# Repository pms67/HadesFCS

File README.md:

# HADES Flight Control System
**Complete flight control system designed from scratch.** The flight control system is primarily designed for fixed-wing, autonomous drones to enable them to perform tasks autonomously, such as take-off, landing, waypoint navigation, payload delivery, etc.

Every part of this system is designed from first principles! This includes the hardware, firmware (using FreeRTOS), Kalman filtering for state estimation, control algorithms, base station, communication protocol, flight simulator, signal processing, and much, much more.

*Feel free to send me constructive criticism or things you would like me to implement, or even if you would like to help me develop this system!*

Intro video: https://www.youtube.com/watch?v=rLDqQ2L_mUQ
       
---

**Broadly, this repository consists of:**
* Hardware designs (developed using KiCAD).
* Low-level drivers and firmware (FreeRTOS, for the STM32 platform of microcontrollers).
* Higher-level firmware such as communication protocols, control and navigation algorithms, etc.
* Kalman filter designs for state estimation.
* Debugging tools.
* Flight simulator (both 6-DOF and 3-DOF) to test algorithms.

---

**Current repository folder structure:**
* *Calibration:* Raw sensor data useful for checking calibration algorithms (e.g. accelerometer bias, scale factor, etc.).
* *Communication:* UAVLink data protocol for reliably packing and transferring data and commands between the aircraft and a further device (e.g. base station). This could be via telemetry or direct serial links.
* *Control:* Algorithms for dynamic control of the aircraft (e.g. PI, state feedback, etc.).
* *Data:* Collection of various datasets that may be useful for offline testing (e.g. raw IMU data).
* *Debug Software:* Tools for interfacing with the hardware (e.g. to read navigation data).
* *Documentation:* Preliminary documents to detail aspects of the flight  control system.
* *Filtering:* FIR and IIR filter implementations, as well as FIR filter design tool.
* *Firmware:* The core flight control firmware running on the STM32 microcontrollers.
* *Flight Simulator:* 6-DOF and 3-DOF fixed-wing flight simulators developed in Unity. Very useful for testing control logic and algorithms. Requires dynamic model of aircraft.
* *GPS:* NMEA sentence parser, as well as raw GPS data for testing.
* *Ground Control:* Basestations written in C# to send commands to aircraft and receive data via telemetry. Includes moving map, live plots, etc.
* *Hardware:* HADES flight control board design files (schematic, layout, assembly). Hardware consists of sensors, microcontrollers, power electronics, etc. This custom hardware is where the firmware runs on.
* *State Estimation*: Kalman filters (various types: quaternion, Euler, different states estimated) designed in Matlab and exported to C for estimation of states required for feedback control (e.g. attitude, position, etc.).
* *Tests:* Miscallaneous tests go here. For instance, device driver testing, communication protocol tests, etc.

**Note:** Most subfolders include an additional README that further describes its contents.

---

**Disclaimer:** This flight control system is work in progress. Use the files, hardware, and software given in this repository **at your own risk** - especially when conducting live flight tests.

BSD 3-Clause License - Copyright (c) 2019, Philip Salmony - All rights reserved.

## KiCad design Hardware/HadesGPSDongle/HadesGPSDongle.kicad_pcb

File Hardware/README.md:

# HADES Hardware

This folder contains all hardware design files for the HADES flight control system.

Currently, there are three designs:

* *Hades:* Dual STM32-based board containing microcontrollers (F4 and H7), inertial sensors, GPS receiver, power distribution system for servos (up to 9A at 5V). This is the main platform for testing.
* *Hades Micro:* 5cmx5cm flight control board with a single STM32F4. No GPS receiver and limited power distribution.
* *Hades Micro (JLCPCB):* Nearly identical to Hades Micro, however uses SPI instead of I2C for sensor communication. Additionally, nearly all parts are available through LCSC/JLCPCB for assembly.

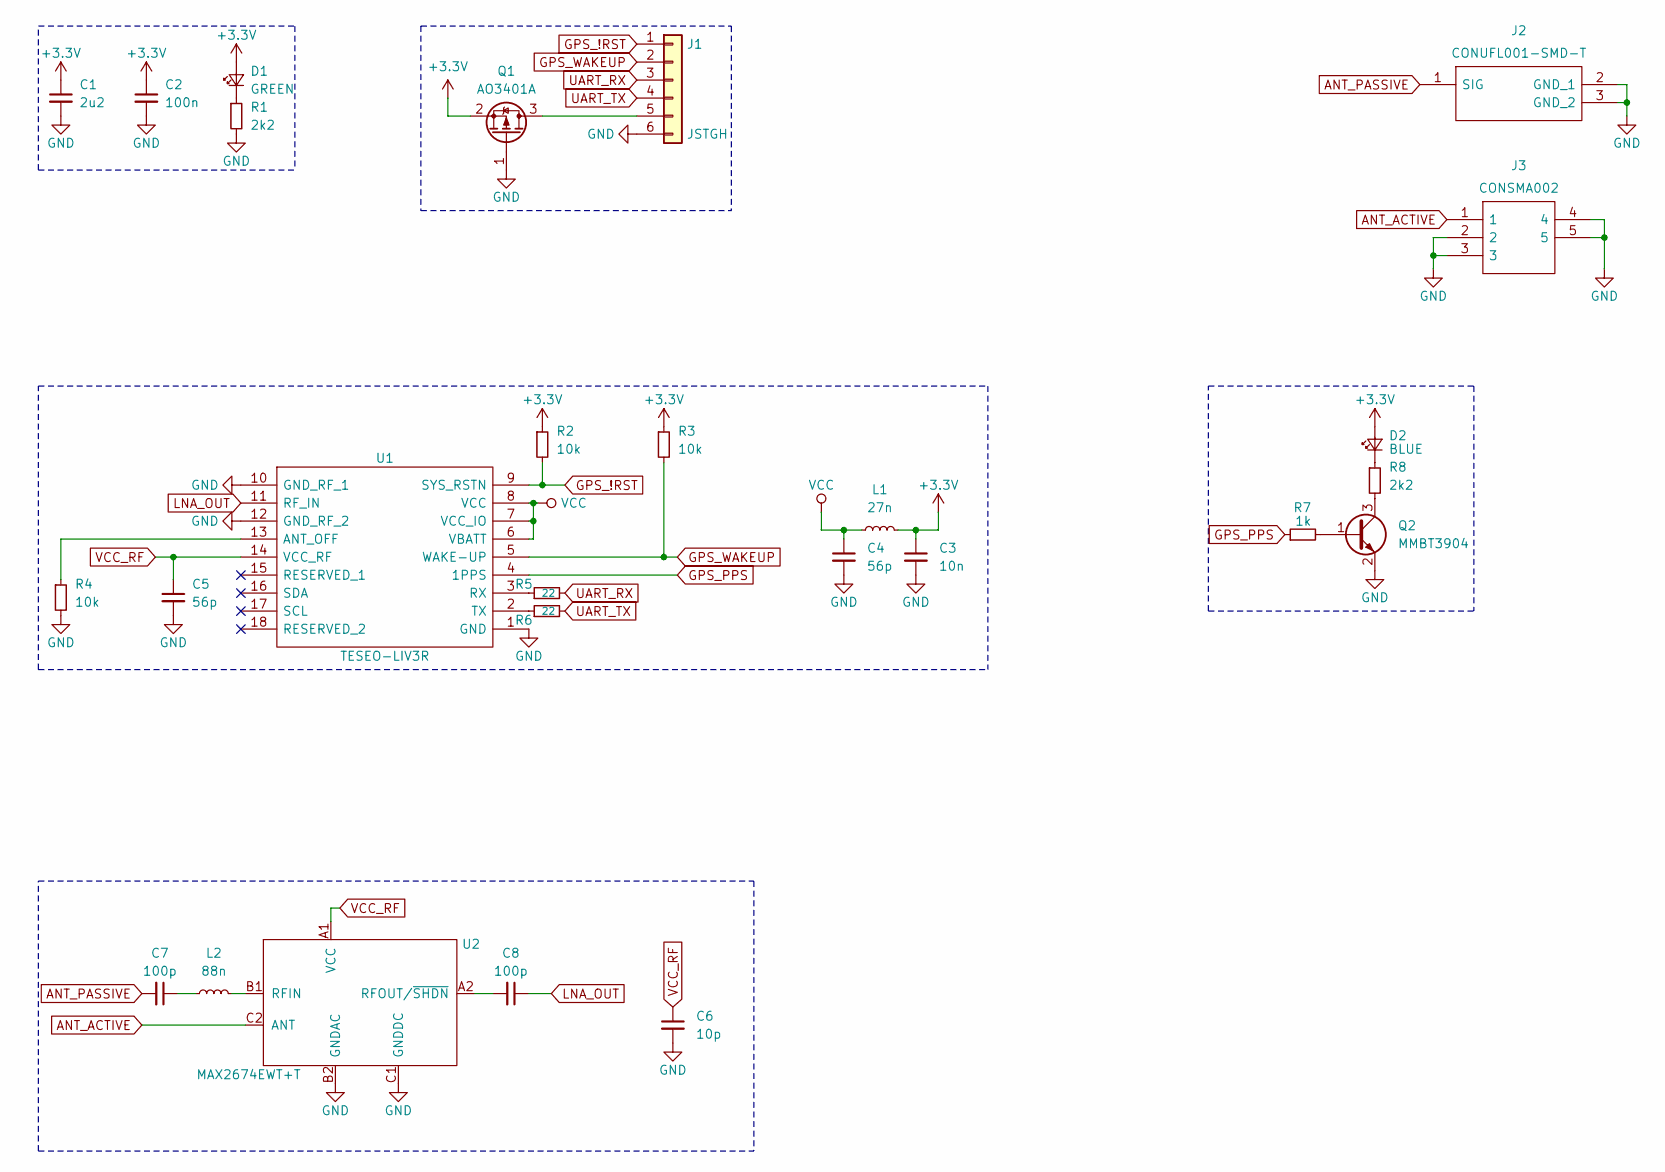
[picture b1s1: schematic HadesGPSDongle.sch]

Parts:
C1: 2u2; C_0603_1608Metric
C2: 100n; C_0402_1005Metric
C3: 10n; C_0402_1005Metric
C4, C5: 56p; C_0402_1005Metric
C6: 10p; C_0402_1005Metric
C7, C8: 100p; C_0402_1005Metric
D1: GREEN; LED_0603_1608Metric
D2: BLUE; LED_0603_1608Metric
J1: JSTGH; JST_GH_SM06B-GHS-TB_1x06-1MP_P1.25mm_Horizontal
J2: CONUFL001-SMD-T; CONUFL001-SMD; Mouser2 Part Number 712-CONUFL001-SMD-T
J3: CONSMA002; Manufacturer_Part_Number CONSMA002
L1: 27n; L_0402_1005Metric
L2: 88n; L_0402_1005Metric
Q1: AO3401A; SOT-23
Q2: MMBT3904; SOT-23
R1, R8: 2k2; R_0603_1608Metric
R2, R3, R4: 10k; R_0603_1608Metric
R5, R6: 22; R_0402_1005Metric
R7: 1k; R_0402_1005Metric
U1: TESEO-LIV3R; TESEOLIV3R; Mouser2 Part Number 511-TESEO-LIV3R
U2: MAX2674EWT+T

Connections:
+3V3: C1.1, C2.1, C3.1, D1.2 (A), D2.2 (A), L1.2, Q1.2 (S), R2.1, R3.1
ANT_ACTIVE: J3.1, U2.C2 (ANT)
ANT_PASSIVE: C7.2, J2.1 (SIG)
GND: C1.2, C2.2, C3.2, C4.2, C5.2, C6.2, J1.6, J2.2 (GND_1), J2.3 (GND_2), J3.2, J3.3, J3.4, J3.5, Q1.1 (G), Q2.2 (E), R1.2, R4.2, U1.1 (GND), U1.10 (GND_RF_1), U1.12 (GND_RF_2), U2.B2 (GNDAC), U2.C1 (GNDDC)
GPS_!RST: J1.1, R2.2, U1.9 (SYS_RSTN)
GPS_PPS: R7.1, U1.4 (1PPS)
GPS_WAKEUP: J1.2, R3.2, U1.5 (WAKE-UP)
LNA_OUT: C8.1, U1.11 (RF_IN)
unnamed: C7.1, L2.1
unnamed: C8.2, U2.A2 (RFOUT/~SHDN)
unnamed: D1.1 (K), R1.1
unnamed: D2.1 (K), R8.1
unnamed: J1.5, Q1.3 (D)
unnamed: L2.2, U2.B1 (RFIN)
unnamed: Q2.1 (B), R7.2
unnamed: Q2.3 (C), R8.2
unnamed: R4.1, U1.13 (ANT_OFF)
unnamed: R5.1, U1.3 (RX)
unnamed: R6.1, U1.2 (TX)
UART_RX: J1.3, R5.2
UART_TX: J1.4, R6.2
VCC: C4.1, L1.1, U1.6 (VBATT), U1.7 (VCC_IO), U1.8 (VCC)
VCC_RF: C5.1, C6.1, U1.14 (VCC_RF), U2.A1 (VCC)

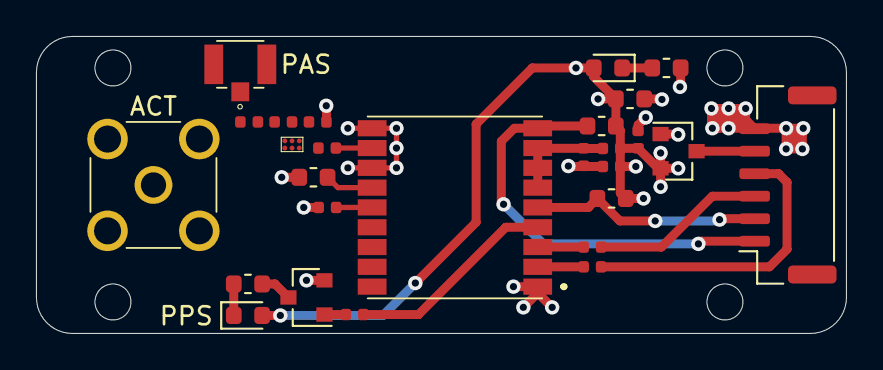
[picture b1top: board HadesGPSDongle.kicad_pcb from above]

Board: 4 copper layers, 45.0 x 16.5 mm, 27 parts (0 on the bottom side), 23 nets.

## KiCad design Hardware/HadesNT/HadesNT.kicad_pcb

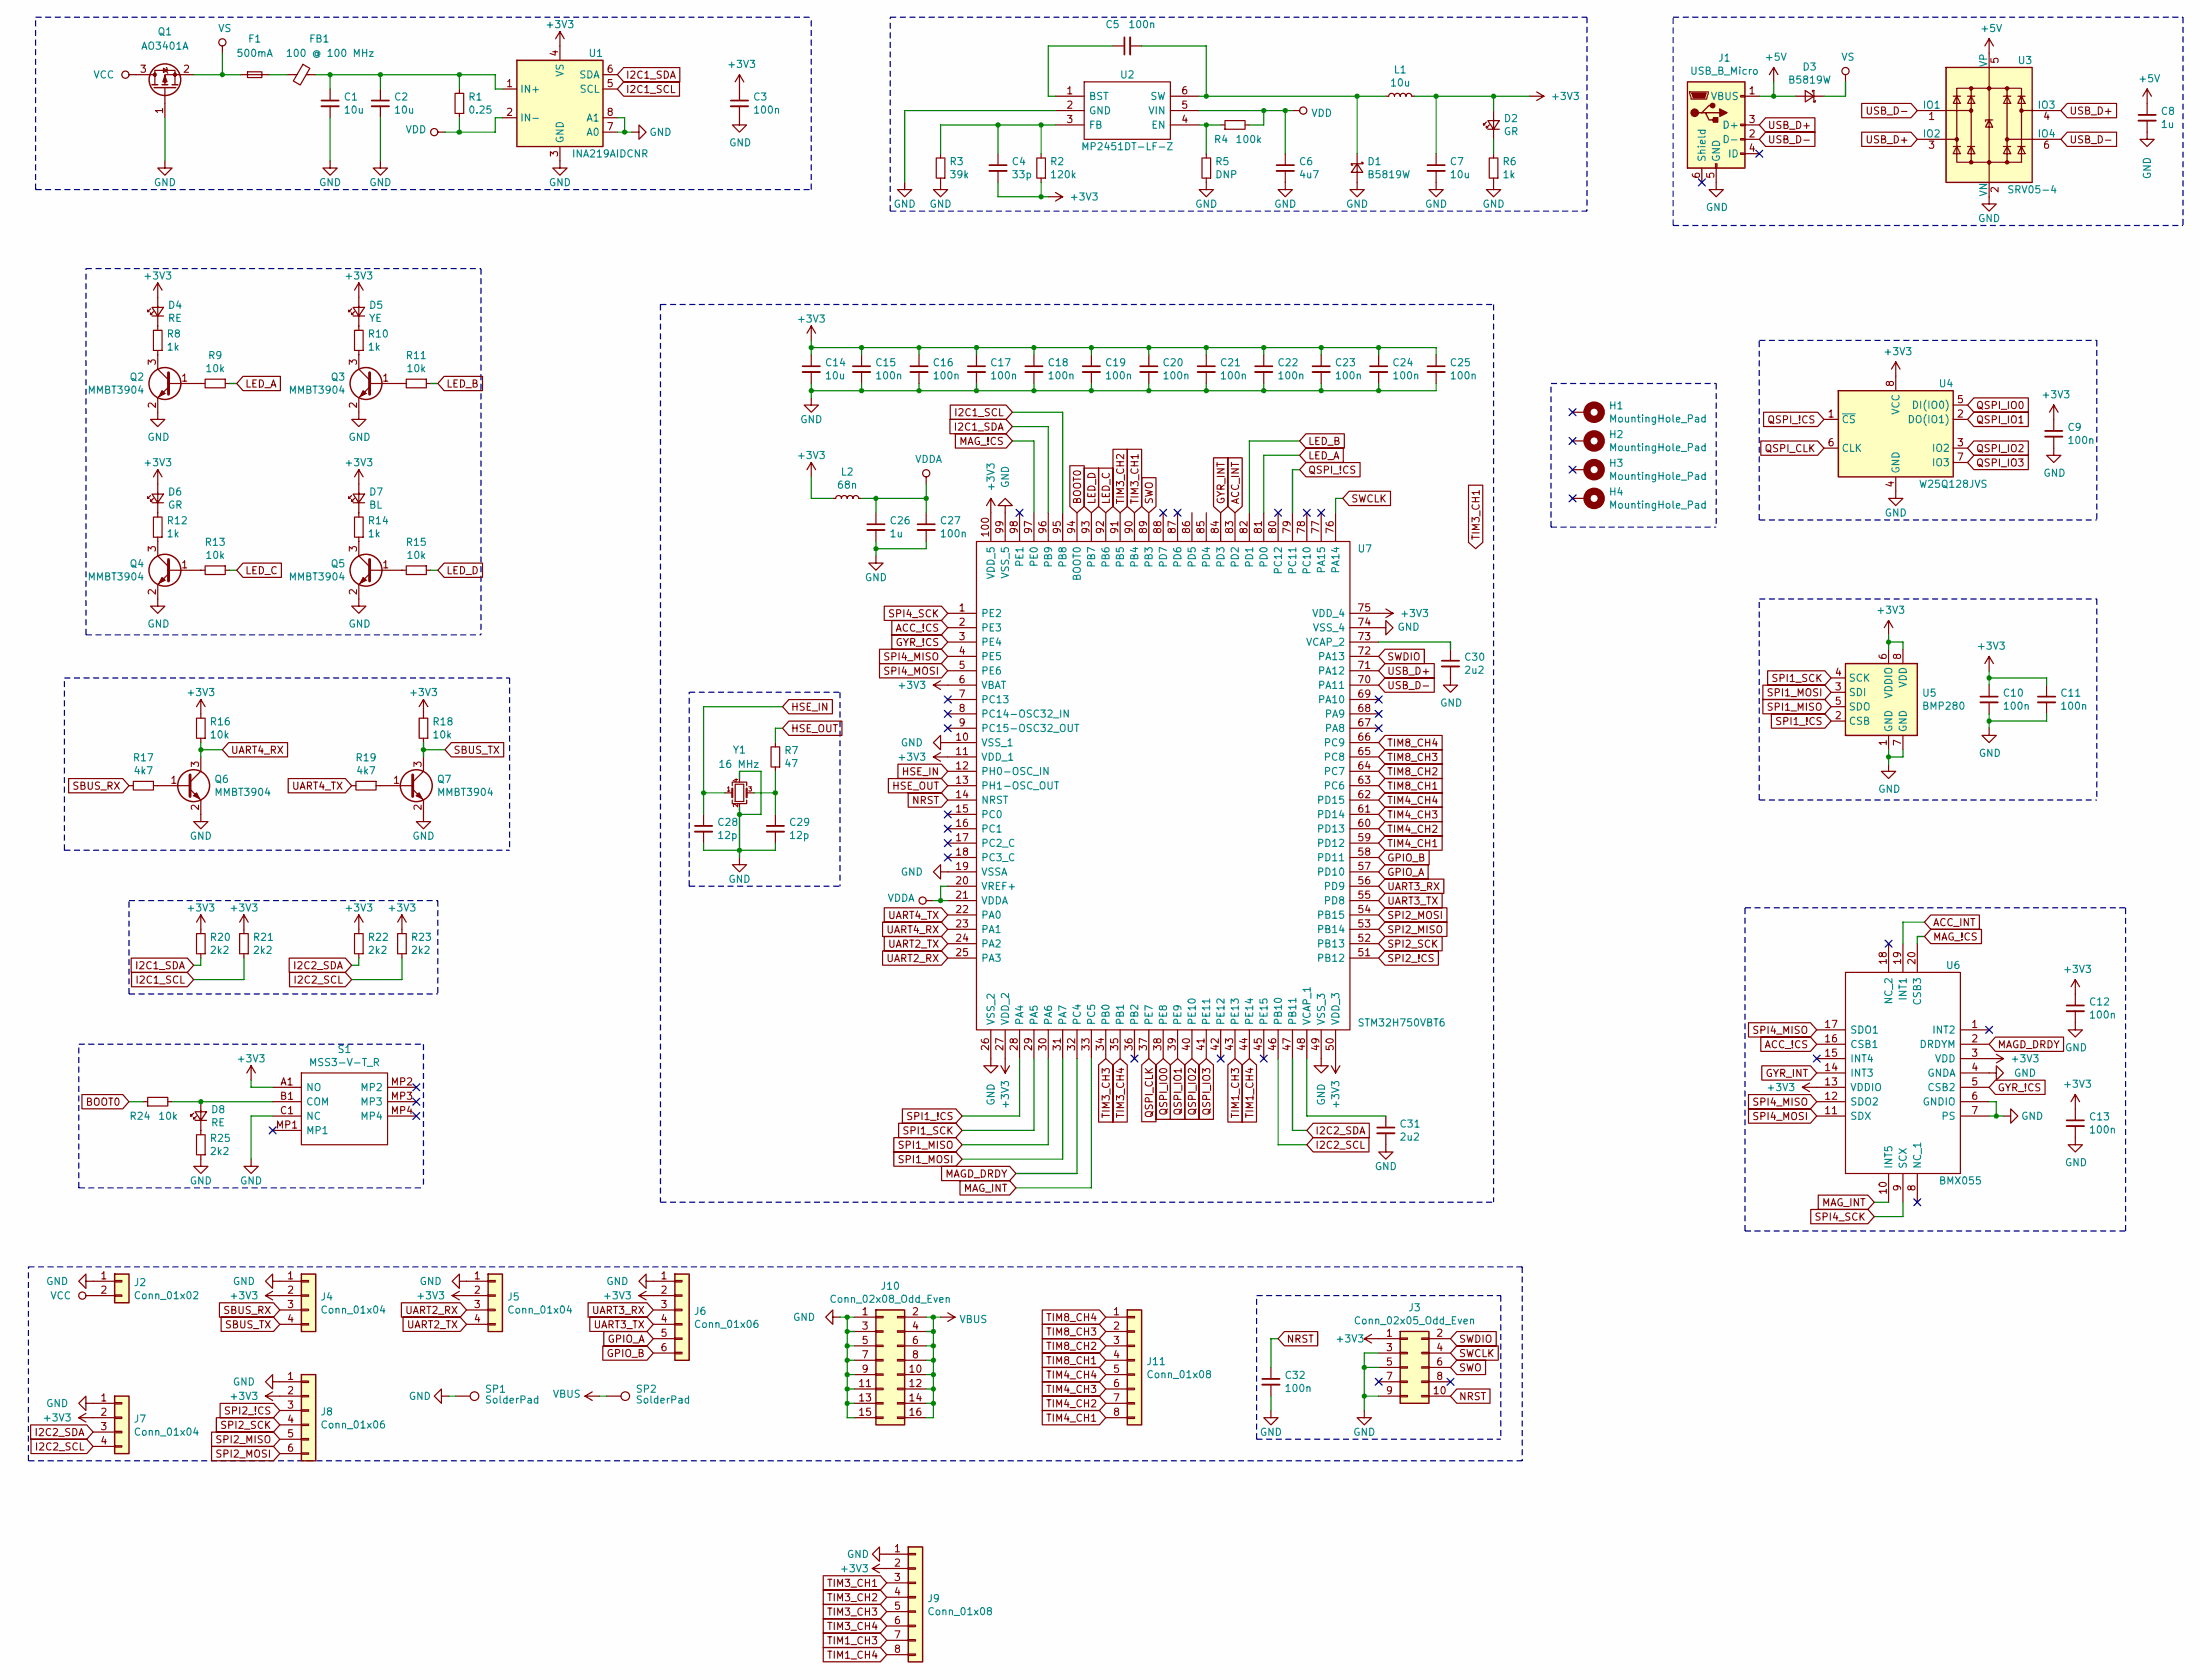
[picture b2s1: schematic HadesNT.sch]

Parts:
C1, C2, C7: 10u; C_1206_3216Metric
C3, C9, C10, C11, C12, C13, C15, C16, C17, C18, C19, C20, C21, C22, C23, C24, C25, C27, C32: 100n; C_0402_1005Metric
C4: 33p; C_0603_1608Metric
C5: 100n; C_0603_1608Metric
C6: 4u7; C_1206_3216Metric
C8: 1u; C_0603_1608Metric
C14: 10u; C_0805_2012Metric
C26: 1u; C_0402_1005Metric
C28, C29: 12p; C_0402_1005Metric
C30, C31: 2u2; C_0603_1608Metric
D1, D3: B5819W; D_SOD-123
D2, D6: GR; LED_0603_1608Metric
D4, D8: RE; LED_0603_1608Metric
D5: YE; LED_0603_1608Metric
D7: BL; LED_0603_1608Metric
F1: 500mA; L_1206_3216Metric
FB1: 100 @ 100 MHz; L_0805_2012Metric
H1, H2, H3, H4: MountingHole_Pad; MountingHole_4.3mm_M4_Pad_Via
J1: USB_B_Micro; 101181930001LF
J2: Conn_01x02; JST_GH_SM02B-GHS-TB_1x02-1MP_P1.25mm_Horizontal
J3: Conn_02x05_Odd_Even; PinHeader_2x05_P1.27mm_Vertical
J4, J5, J7: Conn_01x04; JST_GH_SM04B-GHS-TB_1x04-1MP_P1.25mm_Horizontal
J6, J8: Conn_01x06; JST_GH_SM06B-GHS-TB_1x06-1MP_P1.25mm_Horizontal
J9: Conn_01x08; JST_GH_SM08B-GHS-TB_1x08-1MP_P1.25mm_Horizontal
J10: Conn_02x08_Odd_Even; PinHeader_2x08_P2.54mm_Vertical
J11: Conn_01x08; PinHeader_1x08_P2.54mm_Vertical
L1: 10u; INDPM5452X300N
L2: 68n; L_0402_1005Metric
Q1: AO3401A; SOT-23
Q2, Q3, Q4, Q5, Q6, Q7: MMBT3904; SOT-23
R1: 0.25; R_1206_3216Metric
R2: 120k; R_0603_1608Metric
R3: 39k; R_0603_1608Metric
R4: 100k; R_0402_1005Metric
R5: DNP; R_0402_1005Metric
R6, R8, R10, R12, R14: 1k; R_0603_1608Metric
R7: 47; R_0402_1005Metric
R9, R11, R13, R15, R24: 10k; R_0402_1005Metric
R16, R18: 10k; R_0603_1608Metric
R17, R19: 4k7; R_0402_1005Metric
R20, R21, R22, R23: 2k2; R_0402_1005Metric
R25: 2k2; R_0603_1608Metric
S1: MSS3-V-T_R; MSS3VTR; Mouser2 Part Number 113-MSS3-V-T/R
SP1, SP2: SolderPad; TestPoint_Pad_2.0x2.0mm
U1: INA219AIDCNR; SOT-23-8
U2: MP2451DT-LF-Z; SOT95P280X145-6N; Mouser2 Part Number 946-MP2451DTLFZ
U3: SRV05-4; SOT-23-6
U4: W25Q128JVS; SOIC-8_5.23x5.23mm_P1.27mm
U5: BMP280; Bosch_LGA-8_2x2.5mm_P0.65mm_ClockwisePinNumbering
U6: BMX055; LGA_PACKAGE_20_PINS; Mouser2 Part Number 262-BMX055
U7: STM32H750VBT6; QFP50P1600X1600X160-100N; Manufacturer_Part_Number STM32H750VBT6
Y1: 16 MHz; Crystal_SMD_3225-4Pin_3.2x2.5mm

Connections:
+3V3: C3.1, C4.2, C7.1, C9.1, C10.1, C11.1, C12.1, C13.1, C14.1, C15.1, C16.1, C17.1, C18.1, C19.1, C20.1, C21.1, C22.1, C23.1, C24.1, C25.1, D2.2 (A), D4.2 (A), D5.2 (A), D6.2 (A), D7.2 (A), J3.1, J4.2, J5.2, J6.2, J7.2, J8.2, J9.2, L1.2, L2.1, R2.1, R16.2, R18.2, R20.2, R21.2, R22.2, R23.2, S1.A1 (NO), U1.4 (VS), U4.8 (VCC), U5.6 (VDDIO), U5.8 (VDD), U6.3 (VDD), U6.13 (VDDIO), U7.6 (VBAT), U7.11 (VDD_1), U7.27 (VDD_2), U7.50 (VDD_3), U7.75 (VDD_4), U7.100 (VDD_5)
+5V: C8.1, D3.2 (A), J1.1 (VBUS), U3.5 (VP)
ACC_!CS: U6.16 (CSB1), U7.2 (PE3)
ACC_INT: U6.19 (INT1), U7.83 (PD2)
BOOT0: R24.1, U7.94 (BOOT0)
GND: C1.2, C2.2, C3.2, C6.2, C7.2, C8.2, C9.2, C10.2, C11.2, C12.2, C13.2, C14.2, C15.2, C16.2, C17.2, C18.2, C19.2, C20.2, C21.2, C22.2, C23.2, C24.2, C25.2, C26.2, C27.2, C28.2, C29.2, C30.2, C31.2, C32.2, D1.2 (A), J1.5 (GND), J2.1, J3.3, J3.5, J3.9, J4.1, J5.1, J6.1, J7.1, J8.1, J9.1, J10.1, J10.3, J10.5, J10.7, J10.9, J10.11, J10.13, J10.15, Q1.1 (G), Q2.2 (E), Q3.2 (E), Q4.2 (E), Q5.2 (E), Q6.2 (E), Q7.2 (E), R3.1, R5.1, R6.1, R25.1, S1.C1 (NC), SP1.1, U1.3 (GND), U1.7 (A0), U1.8 (A1), U2.2 (GND), U3.2 (VN), U4.4 (GND), U5.1 (GND), U5.7 (GND), U6.4 (GNDA), U6.6 (GNDIO), U6.7 (PS), U7.10 (VSS_1), U7.19 (VSSA), U7.26 (VSS_2), U7.49 (VSS_3), U7.74 (VSS_4), U7.99 (VSS_5), Y1.2, Y1.4
GPIO_A: J6.5, U7.57 (PD10)
GPIO_B: J6.6, U7.58 (PD11)
GYR_!CS: U6.5 (CSB2), U7.3 (PE4)
GYR_INT: U6.14 (INT3), U7.84 (PD3)
HSE_IN: C28.1, U7.12 (PH0-OSC_IN), Y1.1
HSE_OUT: R7.2, U7.13 (PH1-OSC_OUT)
I2C1_SCL: R21.1, U1.5 (SCL), U7.95 (PB8)
I2C1_SDA: R20.1, U1.6 (SDA), U7.96 (PB9)
I2C2_SCL: J7.4, R23.1, U7.46 (PB10)
I2C2_SDA: J7.3, R22.1, U7.47 (PB11)
LED_A: R9.1, U7.81 (PD0)
LED_B: R11.1, U7.82 (PD1)
LED_C: R13.1, U7.92 (PB6)
LED_D: R15.1, U7.93 (PB7)
MAGD_DRDY: U6.2 (DRDYM), U7.32 (PC4)
MAG_!CS: U6.20 (CSB3), U7.97 (PE0)
MAG_INT: U6.10 (INT5), U7.33 (PC5)
NRST: C32.1, J3.10, U7.14 (NRST)
unnamed: C1.1, C2.1, FB1.1, R1.2, U1.1 (IN+)
unnamed: C4.1, R2.2, R3.2, U2.3 (FB)
unnamed: C5.1, U2.1 (BST)
unnamed: C5.2, D1.1 (K), L1.1, U2.6 (SW)
unnamed: C29.1, R7.1, Y1.3
unnamed: C30.1, U7.73 (VCAP_2)
unnamed: C31.1, U7.48 (VCAP_1)
unnamed: D2.1 (K), R6.2
unnamed: D4.1 (K), R8.2
unnamed: D5.1 (K), R10.2
unnamed: D6.1 (K), R12.2
unnamed: D7.1 (K), R14.2
unnamed: D8.1 (K), R25.2
unnamed: D8.2 (A), R24.2, S1.B1 (COM)
unnamed: F1.2, FB1.2
unnamed: Q2.1 (B), R9.2
unnamed: Q2.3 (C), R8.1
unnamed: Q3.1 (B), R11.2
unnamed: Q3.3 (C), R10.1
unnamed: Q4.1 (B), R13.2
unnamed: Q4.3 (C), R12.1
unnamed: Q5.1 (B), R15.2
unnamed: Q5.3 (C), R14.1
unnamed: Q6.1 (B), R17.1
unnamed: Q7.1 (B), R19.1
unnamed: R4.1, R5.2, U2.4 (EN)
QSPI_!CS: U4.1 (~CS), U7.79 (PC11)
QSPI_CLK: U4.6 (CLK), U7.37 (PE7)
QSPI_IO0: U4.5 (DI(IO0)), U7.38 (PE8)
QSPI_IO1: U4.2 (DO(IO1)), U7.39 (PE9)
QSPI_IO2: U4.3 (IO2), U7.40 (PE10)
QSPI_IO3: U4.7 (IO3), U7.41 (PE11)
SBUS_RX: J4.3, R17.2
SBUS_TX: J4.4, Q7.3 (C), R18.1
SPI1_!CS: U5.2 (CSB), U7.28 (PA4)
SPI1_MISO: U5.5 (SDO), U7.30 (PA6)
SPI1_MOSI: U5.3 (SDI), U7.31 (PA7)
SPI1_SCK: U5.4 (SCK), U7.29 (PA5)
SPI2_!CS: J8.3, U7.51 (PB12)
SPI2_MISO: J8.5, U7.53 (PB14)
SPI2_MOSI: J8.6, U7.54 (PB15)
SPI2_SCK: J8.4, U7.52 (PB13)
SPI4_MISO: U6.12 (SDO2), U6.17 (SDO1), U7.4 (PE5)
SPI4_MOSI: U6.11 (SDX), U7.5 (PE6)
SPI4_SCK: U6.9 (SCX), U7.1 (PE2)
SWCLK: J3.4, U7.76 (PA14)
SWDIO: J3.2, U7.72 (PA13)
SWO: J3.6, U7.89 (PB3)
TIM1_CH3: J9.7, U7.43 (PE13)
TIM1_CH4: J9.8, U7.44 (PE14)
TIM3_CH1: J9.3, U7.90 (PB4)
TIM3_CH2: J9.4, U7.91 (PB5)
TIM3_CH3: J9.5, U7.34 (PB0)
TIM3_CH4: J9.6, U7.35 (PB1)
TIM4_CH1: J11.8, U7.59 (PD12)
TIM4_CH2: J11.7, U7.60 (PD13)
TIM4_CH3: J11.6, U7.61 (PD14)
TIM4_CH4: J11.5, U7.62 (PD15)
TIM8_CH1: J11.4, U7.63 (PC6)
TIM8_CH2: J11.3, U7.64 (PC7)
TIM8_CH3: J11.2, U7.65 (PC8)
TIM8_CH4: J11.1, U7.66 (PC9)
UART2_RX: J5.3, U7.25 (PA3)
UART2_TX: J5.4, U7.24 (PA2)
UART3_RX: J6.3, U7.56 (PD9)
UART3_TX: J6.4, U7.55 (PD8)
UART4_RX: Q6.3 (C), R16.1, U7.23 (PA1)
UART4_TX: R19.2, U7.22 (PA0)
USB_D+: J1.3 (D+), U3.3 (IO2), U3.4 (IO3), U7.71 (PA12)
USB_D-: J1.2 (D-), U3.1 (IO1), U3.6 (IO4), U7.70 (PA11)
VBUS: J10.2, J10.4, J10.6, J10.8, J10.10, J10.12, J10.14, J10.16, SP2.1
VCC: J2.2, Q1.3 (D)
VDD: C6.1, R1.1, R4.2, U1.2 (IN-), U2.5 (VIN)
VDDA: C26.1, C27.1, L2.2, U7.20 (VREF+), U7.21 (VDDA)
VS: D3.1 (K), F1.1, Q1.2 (S)

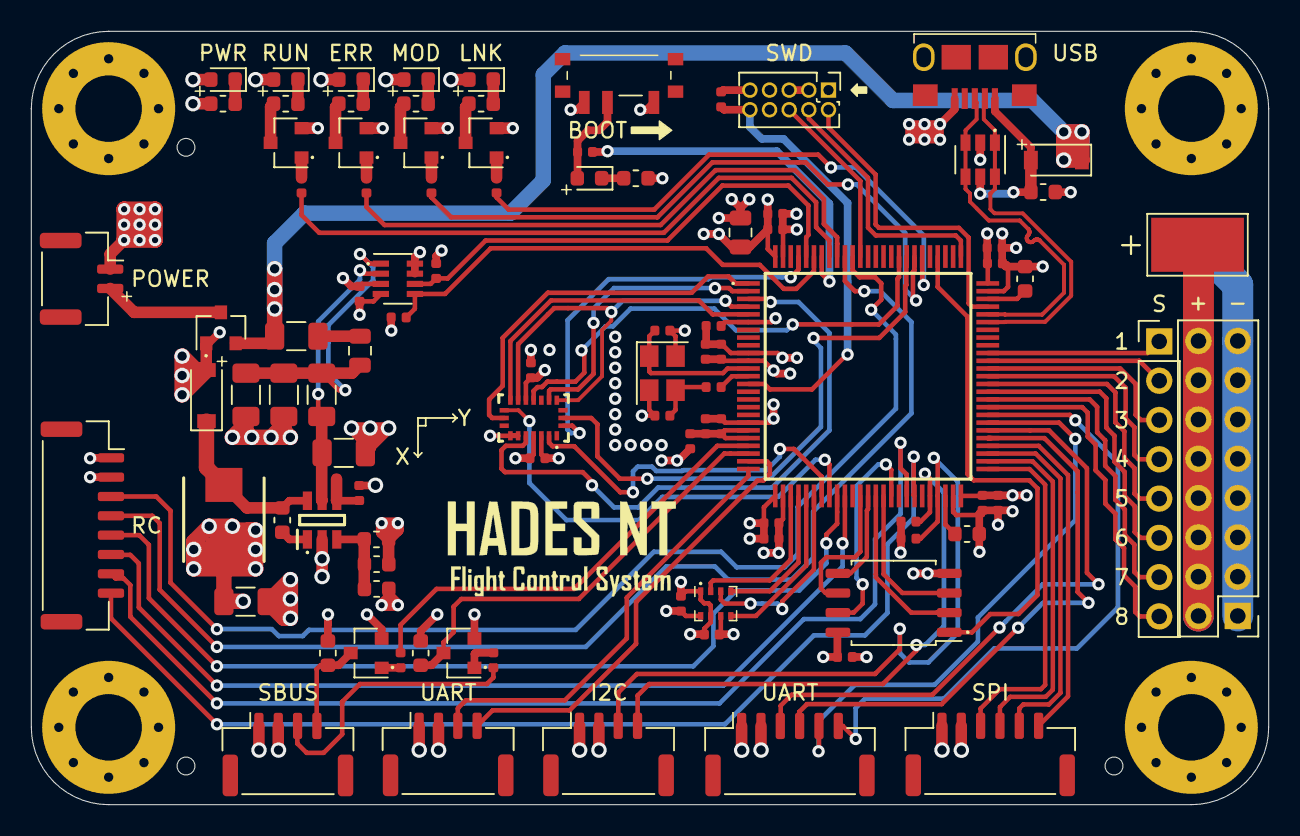
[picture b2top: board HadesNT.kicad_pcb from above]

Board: 4 copper layers, 80.0 x 50.0 mm, 102 parts (1 on the bottom side), 99 nets.

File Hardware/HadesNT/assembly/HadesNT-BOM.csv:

Designator,Quantity,Value,Footprint,LCSC Part #
"C1, C2, C7, ",3,10u,1206,C13585
"C3, C9, C10, C11, C12, C13, C15, C16, C17, C18, C19, C20, C21, C22, C23, C24, C25, C27, C32, ",19,100n,0402,C1525
"C4, ",1,33p,0603,C1663
"C5, ",1,100n,0603,C14663
"C6, ",1,4u7,1206,C29823
"C8, ",1,1u,0603,C15849
"C14, ",1,10u,0805,C15850
"C26, ",1,1u,0402,C52923
"C28, C29, ",2,12p,0402,C1547
"C30, C31, ",2,2u2,0603,C23630
"D1, D3, ",2,B5819W,SOD-123,C8598
"D2, D6, ",2,GR,0603,C72043
"D4, D8, ",1,RE,0603,C2286
"D5, ",1,YE,0603,C72038
"D7, ",1,BL,0603,C72041
"F1, ",1,500mA,1206,C369155
"FB1, ",1,100 @ 100 MHz,0805,C1015
"L1, ",1,10u,SMD-PIND-5.2x5.4x2.8_1.2x2.2,C139506
"L2, ",1,68n,0402,C26443
"Q1, ",1,AO3401A,SOT-23-3L,C15127
"Q2, Q3, Q4, Q5, Q6, Q7, ",6,MMBT3904,SOT-23-3,C20526
"R1, ",1,0.25,1206,C247450
"R2, ",1,120k,0603,C25808
"R3, ",1,39k,0603,C23153
"R4, ",1,100k,0402,C25741
"R6, R8, R10, R12, R14, R25, ",5,1k,0603,C21190
"R7, ",1,47,0402,C25118
"R9, R11, R13, R15, R24, ",5,10k,0402,C25744
"R16, R18, ",2,10k,0603,C25804
"R17, R19, ",2,4k7,0402,C25900
"R20, R21, R22, R23, ",4,2k2,0402,C25879
"U1, ",1,INA219AIDCNR,SOT-23-8,C87469
"U2, ",1,MP2451DT-LF-Z,SOT-23-6L,C14123
"U3, ",1,SRV05-4,SOT-23-6L,C85364
"U4, ",1,W25Q128JVS,SOIC-8_5.3x5.3x1.27P,C97521
"U5, ",1,BMP280,LGA-8_2.0x2.5x0.65P,C83291
"U6, ",1,BMX055,LGA-20_3.0x4.5x0.5P,C94022
"U7, ",1,STM32H750VBT6,LQFP-100_14.0x14.0x0.5P,C404010
"Y1, ",1,16 MHz,SMD-3225_4P,C13738

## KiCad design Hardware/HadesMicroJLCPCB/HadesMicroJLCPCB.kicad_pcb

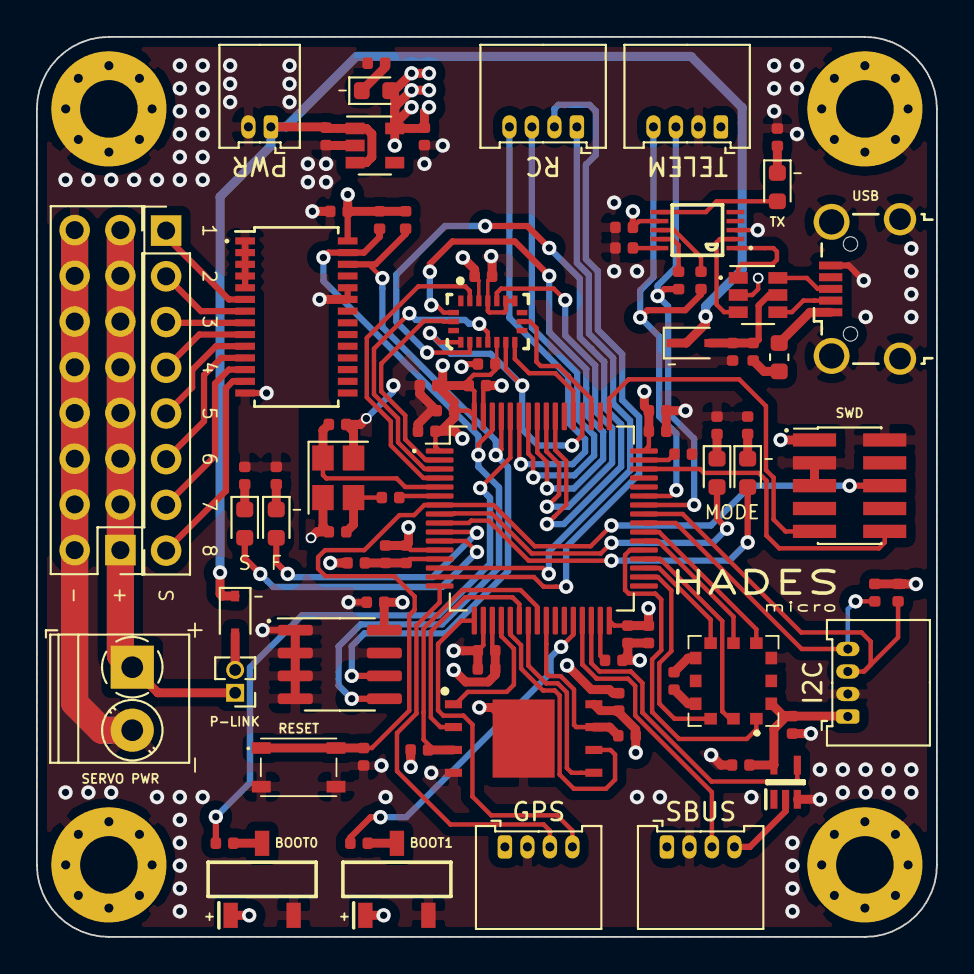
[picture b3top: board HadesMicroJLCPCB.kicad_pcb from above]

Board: 4 copper layers, 50.0 x 50.0 mm, 84 parts (0 on the bottom side), 85 nets.

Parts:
BOOT1, BOOT2: TDD01H0SB1R; SOT175P420X230-3N
C1, C2, C22: 1u; C_0402_1005Metric
C3: 10u; C_0402_1005Metric
C4, C5, C6, C7, C8, C9, C10, C11, C12, C13, C16, C17, C18, C19, C23, C25, C26, C27, C28, C29, C30: 100n; C_0402_1005Metric
C14, C15: 2u2; C_0402_1005Metric
C20, C21: 10p; C_0402_1005Metric
C24: 1n; C_0402_1005Metric
D1, D6: D_Schottky; D_SOD-323
D2: GR; LED_0603_1608Metric
D3: RE; LED_0603_1608Metric
D4, D5: BL; LED_0603_1608Metric
D7: YE; LED_0603_1608Metric
F1: Fuse; Fuse_0603_1608Metric
FB1, FB2: FB_Small; L_0402_1005Metric
FLASH1: W25N01GVZEIG_TR; SON127P800X600X80-9N-D
GPS: Conn_01x04; Molex_PicoBlade_53048-0410_1x04_P1.25mm_Horizontal
HSE1: 16MHz; Crystal_SMD_Abracon_ABM8G-4Pin_3.2x2.5mm
I2C: Conn_01x04; Molex_PicoBlade_53048-0410_1x04_P1.25mm_Horizontal
IC1: MPRLS0015PA0000SA
IMU1: BMX055; LGA_PACKAGE_20_PINS
JP1: Jumper_NO_Small; PinHeader_1x02_P1.27mm_Vertical
MCU: STM32F405RGT6; LQFP-64_10x10mm_P0.5mm
PWM_PWR1: Conn_02x08_Odd_Even; PinHeader_2x08_P2.54mm_Vertical
PWM_SIGNAL1: Conn_01x08; PinHeader_1x08_P2.54mm_Vertical
PWR: Conn_01x02; Molex_PicoBlade_53048-0210_1x02_P1.25mm_Horizontal
PWR1: GR; LED_0603_1608Metric
R1, R2, R6, R7, R8, R9, R15: 2k2; R_0402_1005Metric
R3, R4, R5: 1k; R_0402_1005Metric
R10: 620; R_0402_1005Metric
R11, R13: 22; R_0402_1005Metric
R12, R14, R16, R17: 10k; R_0402_1005Metric
RC: Conn_01x04; Molex_PicoBlade_53048-0410_1x04_P1.25mm_Horizontal
RESET1: SKRPANE010; SKRPADE010
SBUS: Conn_01x04; Molex_PicoBlade_53048-0410_1x04_P1.25mm_Horizontal
SERVO1: TrmnlBlck; TerminalBlock_Phoenix_PT-1,5-2-3.5-H_1x02_P3.50mm_Horizontal
SWD: Conn_02x05_Counter_Clockwise; PinHeader_2x05_P1.27mm_Vertical_SMD
TELEM: Conn_01x04; Molex_PicoBlade_53048-0410_1x04_P1.25mm_Horizontal
U1: AP2112K-3.3; SOT-23-5
U2: PCA9685PW; TSSOP-28_4.4x9.7mm_P0.65mm
U3: CAT24C256; SOIC-8_3.9x4.9mm_P1.27mm
U4: USBLC6-2SC6; SOT-23-6
U5: 74AHC1GU04GW,125; SOT65P212X110-5N
U6: CH340E; MSOP10
USB: USB_B_Micro; USB_Micro-B_Wuerth_629105150521_CircularHoles

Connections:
+3V3: BOOT1.1, BOOT2.1, C2.1, C3.1, C4.1, C5.1, C6.1, C7.1, C8.1, C9.1, C10.1, C11.1, C12.1, C13.1, C16.1, C18.1, C19.1, C25.2, C27.1, C28.1, C29.1, FB2.2, FLASH1.8, GPS.1, I2C.1, IC1.12, IMU1.3, IMU1.13, MCU.1, MCU.19, MCU.32, MCU.48, MCU.64, PWR1.2, R6.1, R7.1, R8.1, R9.1, R12.1, R14.2, SBUS.1, SWD.1, TELEM.1, U1.5, U2.28, U3.8, U5.5, U6.7
BAR_NRST: IC1.9, MCU.39
BOOT0: MCU.60, R16.2
BOOT1: MCU.28, R17.2
FLASH_!H: FLASH1.7, MCU.25, R14.1
FLASH_!WP: FLASH1.3, MCU.24, R12.2
GND: BOOT1.2, BOOT2.2, C1.2, C2.2, C3.2, C4.2, C5.2, C6.2, C7.2, C8.2, C9.2, C10.2, C11.2, C12.2, C13.2, C14.2, C15.2, C16.2, C17.2, C18.2, C19.2, C20.2, C21.2, C22.2, C23.2, C25.1, C26.2, C27.2, C28.2, C29.2, C30.2, FLASH1.4, FLASH1.9, GPS.2, HSE1.2, HSE1.4, I2C.2, IC1.10, IMU1.4, IMU1.6, IMU1.7, MCU.12, MCU.18, MCU.63, PWM_PWR1.2, PWM_PWR1.4, PWM_PWR1.6, PWM_PWR1.8, PWM_PWR1.10, PWM_PWR1.12, PWM_PWR1.14, PWM_PWR1.16, PWR.2, R1.1, R2.2, R3.2, R4.2, R5.2, R15.1, RESET1.3, RESET1.4, SBUS.2, SERVO1.2, SWD.2, SWD.3, SWD.5, TELEM.2, U1.2, U2.1, U2.2, U2.3, U2.4, U2.5, U2.14, U2.23, U2.24, U3.1, U3.2, U3.3, U3.4, U3.7, U4.2, U5.3, U6.3, USB.5, USB.6
HSE_IN: C20.1, HSE1.1, MCU.5
HSE_OUT: MCU.6, R10.1
I2C1_SCL: MCU.61, R6.2, U2.26, U3.6
I2C1_SDA: MCU.62, R7.2, U2.27, U3.5
I2C3_SCL: I2C.3, MCU.41, R8.2
I2C3_SDA: I2C.4, MCU.40, R9.2
INT_ACC: IMU1.19, MCU.2
INT_BAR: IC1.8, MCU.38
INT_GYR: IMU1.14, MCU.3
INT_MAG: IMU1.2, MCU.4
LED_A: D2.2, MCU.8
LED_B: D3.2, MCU.9
LED_C: D4.2, MCU.10
LED_D: D5.2, MCU.11
NRST: C30.1, MCU.7, RESET1.1, RESET1.2, SWD.6
unnamed: BOOT1.3, R16.1
unnamed: BOOT2.3, R17.1
unnamed: C14.1, MCU.31
unnamed: C15.1, MCU.47
unnamed: C17.1, D6.2, FB1.1, U4.5
unnamed: C21.1, HSE1.3, R10.2
unnamed: C24.1, IC1.6
unnamed: C24.2, IC1.4
unnamed: C26.1, U6.10
unnamed: D1.2, JP1.2
unnamed: D2.1, R2.1
unnamed: D3.1, R3.1
unnamed: D4.1, R4.1
unnamed: D5.1, R5.1
unnamed: D7.1, R15.2
unnamed: D7.2, U6.6
unnamed: F1.1, FB1.2
unnamed: F1.2, USB.1
unnamed: JP1.1, PWM_PWR1.1, PWM_PWR1.3, PWM_PWR1.5, PWM_PWR1.7, PWM_PWR1.9, PWM_PWR1.11, PWM_PWR1.13, PWM_PWR1.15, SERVO1.1
unnamed: PWM_SIGNAL1.1, U2.6
unnamed: PWM_SIGNAL1.2, U2.7
unnamed: PWM_SIGNAL1.3, U2.8
unnamed: PWM_SIGNAL1.4, U2.9
unnamed: PWM_SIGNAL1.5, U2.10
unnamed: PWM_SIGNAL1.6, U2.11
unnamed: PWM_SIGNAL1.7, U2.12
unnamed: PWM_SIGNAL1.8, U2.13
unnamed: PWR1.1, R1.2
unnamed: R11.2, U6.9
unnamed: R13.2, U6.8
SPI1_CS: FLASH1.1, MCU.20
SPI1_MISO: FLASH1.2, MCU.22
SPI1_MOSI: FLASH1.5, MCU.23
SPI1_SCK: FLASH1.6, MCU.21
SPI2_CS: IC1.1, MCU.37
SPI2_MISO: IC1.7, MCU.35
SPI2_MOSI: IC1.2, MCU.36
SPI2_SCK: IC1.3, MCU.34
SPI3_CSACC: IMU1.16, MCU.55
SPI3_CSGYR: IMU1.5, MCU.56
SPI3_CSMAG: IMU1.20, MCU.57
SPI3_MISO: IMU1.12, IMU1.17, MCU.52
SPI3_MOSI: IMU1.11, MCU.53
SPI3_SCK: IMU1.9, MCU.51
SWCLK: MCU.49, SWD.9
SWDIO: MCU.46, SWD.10
TIM2_CH1: MCU.14, RC.1
TIM2_CH2: MCU.15, RC.2
TIM4_CH1: MCU.58, RC.3
TIM4_CH2: MCU.59, RC.4
UART1_RX: MCU.43, R13.1, TELEM.4
UART1_TX: MCU.42, R11.1, TELEM.3
UART2_RX: GPS.4, MCU.17
UART2_TX: GPS.3, MCU.16
UART3_RX: MCU.30, U5.4
UART3_RX_INV: SBUS.4, U5.2
UART3_TX: MCU.29, SBUS.3
USB_CONN_D+: U4.6, USB.3
USB_CONN_D-: U4.4, USB.2
USB_CONV_D+: U4.1, U6.1
USB_CONV_D-: U4.3, U6.2
VCC: C1.1, D1.1, D6.1, PWR.1, U1.1, U1.3
VDDA: C22.1, C23.1, FB2.1, MCU.13

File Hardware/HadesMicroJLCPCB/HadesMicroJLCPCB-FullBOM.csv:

Reference, Quantity, Value,Assembled?,Supplier,Cost per Part (USD),Cost per Board (USD)
BOOT1 BOOT2 ,2,TDD01H0SB1R,N,LCSC,0.98,1.96
C14 C15 ,2,2u2,N,Mouser,0.35,0.7
C20 C21 ,2,10p,Y,JLCPCB,0.037,0.074
C22 C1 C2 ,3,1u,Y,JLCPCB,0.0022,0.0066
C23 C4 C5 C6 C7 C8 C9 C10 C11 C12 C18 C19 C25 C16 C28 C13 C30 C29 C17 C26 C27 ,21,100n,Y,JLCPCB,0.0017,0.0357
C24 ,1,1n,Y,JLCPCB,0.012,0.012
C3 ,1,10u,Y,JLCPCB,0.091,0.091
D3 ,1,RE,N,LCSC,0.02,0.02
D4 D5 ,2,BL,N,LCSC,0.02,0.04
D6 D1 ,2,D_Schottky,N,LCSC,0.03,0.06
D7 ,1,YE,N,LCSC,0.02,0.02
F1 ,1,Fuse,N,LCSC,0.03,0.03
FB2 FB1 ,2,FB_Small,Y,JLCPCB,0.019,0.038
FLASH1 ,1,W25N01GVZEIG_TR,Y,JLCPCB,1.22,1.22
HSE1 ,1,16MHz,Y,JLCPCB,1.99,1.99
I2C1 RC1 SBUS1 GPS1 TELEM1 ,5,Conn_01x04,N,Mouser,0.47,2.35
IC1 ,1,MPRLS0015PA0000SA,N,Mouser,9.57,9.57
IMU1 ,1,BMX055,Y,JLCPCB,4.5,4.5
JP1 ,1,Jumper_NO_Small,N,Mouser,0.13,0.13
MCU1 ,1,STM32F405RGT6,Y,JLCPCB,4.21,4.21
PWM_PWR1 ,1,Conn_03x08,N,Mouser,1.93,1.93
PWR1 D2 ,2,GR,N,LCSC,0.02,0.04
R10 ,1,470,Y,JLCPCB,0.0072,0.0072
R13 R11 ,2,22,Y,JLCPCB,0.0032,0.0064
R14 R12 R16 R17 ,4,10k,Y,JLCPCB,0.0016,0.0064
R3 R4 R5 ,3,1k,Y,JLCPCB,0.0022,0.0066
R6 R7 R8 R9 R1 R2 R15 ,7,2k2,Y,JLCPCB,0.001,0.007
RESET1 ,1,SKRPANE010,N,Mouser,0.55,0.55
SERVO1 ,1,TrmnlBlck,N,Mouser,0.57,0.57
SWD1 ,1,Conn_02x05_Counter_Clockwise,N,LCSC,0.51,0.51
U1 ,1,AP2112K-3.3,Y,JLCPCB,0.48,0.48
U2 ,1,PCA9685PW,N,Mouser,2.7,2.7
U3 ,1,CAT24C256,Y,JLCPCB,0.26,0.26
U4 ,1,USBLC6-2SC6,Y,JLCPCB,0.15,0.15
U5 ,1,"74AHC1GU04GW,125",Y,JLCPCB,0.1,0.1
U6 ,1,CH340E,Y,JLCPCB,0.4,0.4
USB1 ,1,USB_B_Micro,N,Mouser,2.51,2.51
VIN1 ,1,Conn_01x02,N,Mouser,0.31,0.31
,,,,,,
,,,,,Total Component Cost per Board (USD),37.6

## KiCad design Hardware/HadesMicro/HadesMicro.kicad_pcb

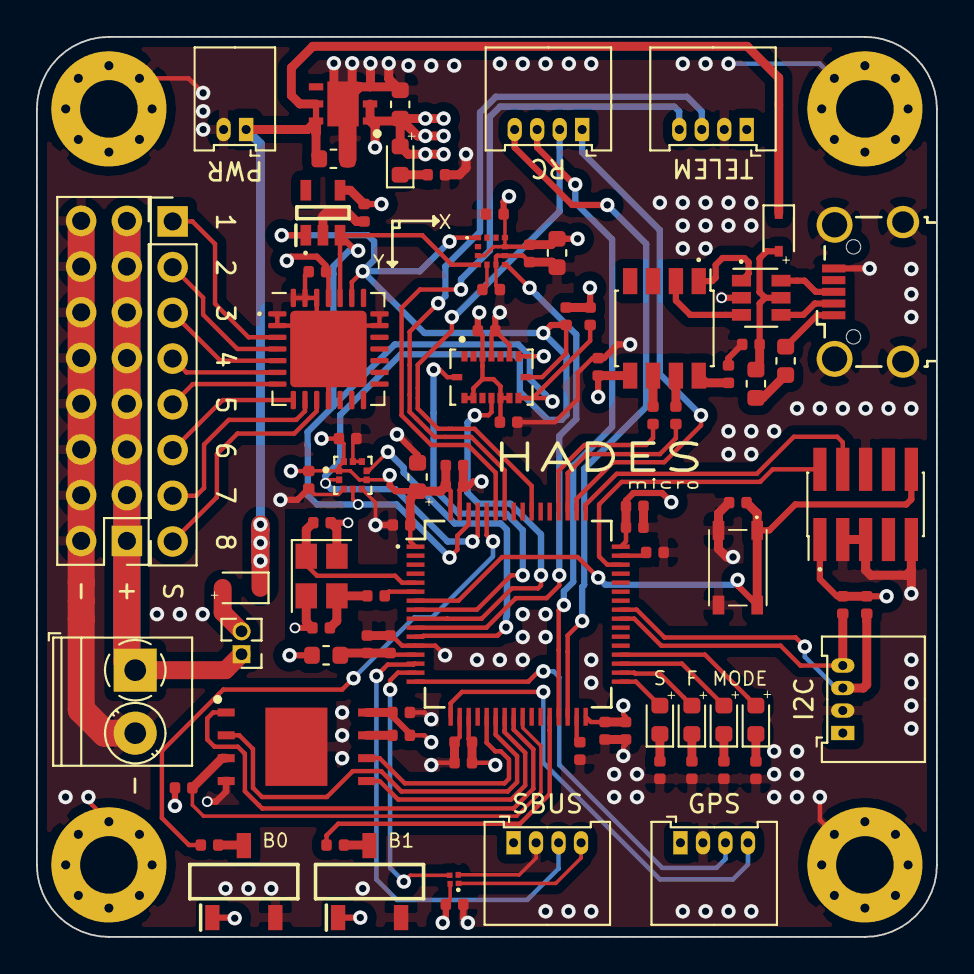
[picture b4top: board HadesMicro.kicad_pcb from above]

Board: 4 copper layers, 50.0 x 50.0 mm, 6 parts (0 on the bottom side), 2 nets.

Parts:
GPS: Conn_01x04; Molex_PicoBlade_53048-0810_1x04_P1.25mm_Horizontal
I2C: Conn_01x04; Molex_PicoBlade_53048-0810_1x04_P1.25mm_Horizontal
PWR: Conn_01x02; Molex_PicoBlade_53048-0410_1x02_P1.25mm_Horizontal
SBUS: Conn_01x04; Molex_PicoBlade_53048-0810_1x04_P1.25mm_Horizontal
SWD: Conn_02x05_Counter_Clockwise; PinHeader_2x05_P1.27mm_Vertical_SMD
TELEM: Conn_01x04; Molex_PicoBlade_53048-0810_1x04_P1.25mm_Horizontal

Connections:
+3V3: GPS.1, I2C.1, SBUS.1, SWD.1, TELEM.1
GND: GPS.2, I2C.2, PWR.2, SBUS.2, SWD.3, SWD.5, SWD.6, SWD.9, TELEM.2
